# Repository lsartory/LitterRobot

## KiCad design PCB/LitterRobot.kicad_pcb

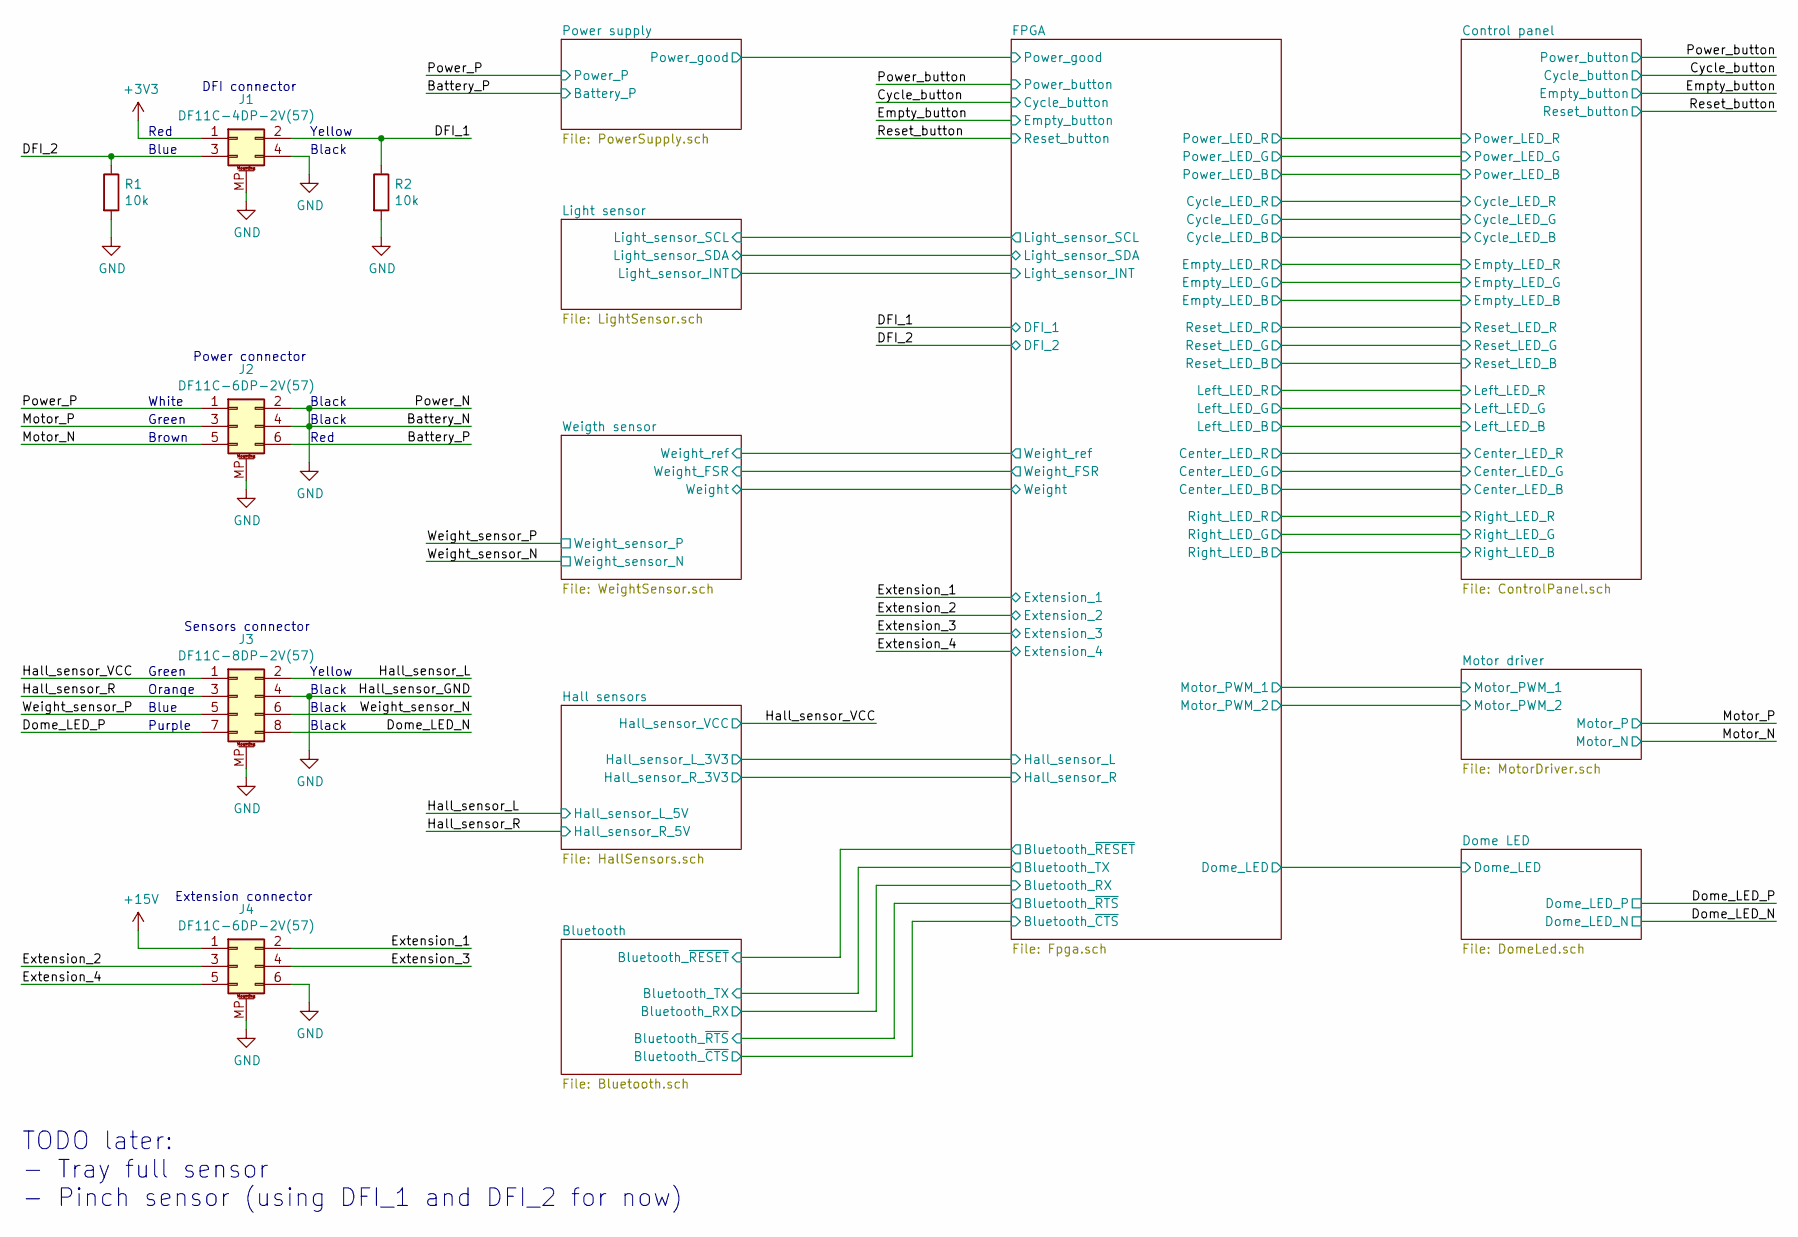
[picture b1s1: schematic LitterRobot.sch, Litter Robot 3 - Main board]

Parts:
J1: DF11C-4DP-2V(57); Hirose_DF11C-4DP-2V(57); Part_number DF11C-4DP-2V(57)
J2, J4: DF11C-6DP-2V(57); Hirose_DF11C-6DP-2V(57); Part_number DF11C-6DP-2V(57)
J3: DF11C-8DP-2V(57); Hirose_DF11C-8DP-2V(57); Part_number DF11C-8DP-2V(57)
R1, R2: 10k; R_0603_1608Metric; Part_number CR0603-FX-1002ELF

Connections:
+3V3: J1.1; also elsewhere on the board
+15V: J4.1; also elsewhere on the board
/Battery_P: J2.6; also elsewhere on the board
/DFI_1: J1.2, R2.1; also elsewhere on the board
/DFI_2: J1.3, R1.1; also elsewhere on the board
/Dome_LED_N: J3.8; also elsewhere on the board
/Dome_LED_P: J3.7; also elsewhere on the board
/Extension_1: J4.2; also elsewhere on the board
/Extension_2: J4.3; also elsewhere on the board
/Extension_3: J4.4; also elsewhere on the board
/Extension_4: J4.5; also elsewhere on the board
/Hall_sensor_L: J3.2; also elsewhere on the board
/Hall_sensor_R: J3.3; also elsewhere on the board
/Hall_sensor_VCC: J3.1; also elsewhere on the board
/Motor_N: J2.5; also elsewhere on the board
/Motor_P: J2.3; also elsewhere on the board
/Power_P: J2.1; also elsewhere on the board
/Weight_sensor_N: J3.6; also elsewhere on the board
/Weight_sensor_P: J3.5; also elsewhere on the board
GND: J1.4, J1.MP (MountPin), J2.2, J2.4, J2.MP (MountPin), J3.4, J3.MP (MountPin), J4.6, J4.MP (MountPin), R1.2, R2.2; also elsewhere on the board

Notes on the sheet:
Red
Blue
Yellow
Black
DFI connector
Power connector
White
Green
Brown
Sensors connector
Orange
Purple
Extension connector
TODO later: - Tray full sensor - Pinch sensor (using DFI_1 and DFI_2 for now)

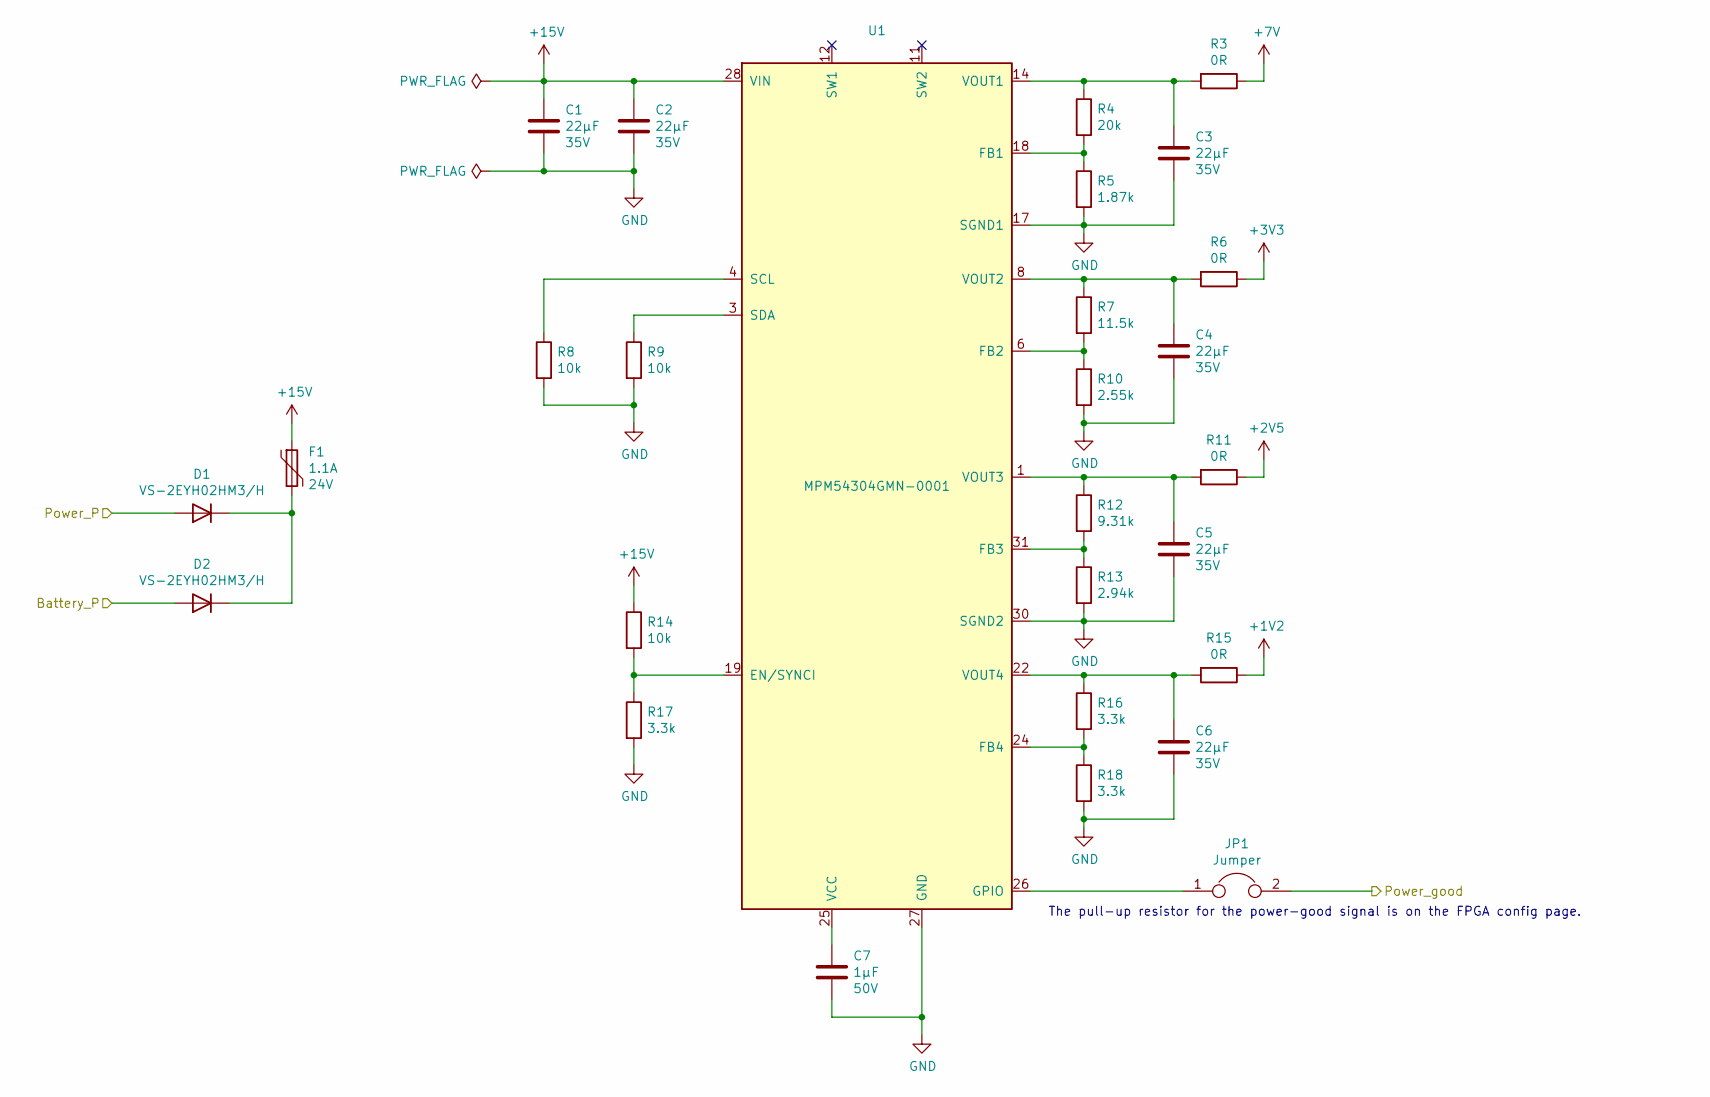
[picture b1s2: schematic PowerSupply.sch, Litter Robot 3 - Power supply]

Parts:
C1, C2, C3, C4, C5, C6: 22µF; C_1206_3216Metric; Voltage 35V; Part_number C3216X5R1V226M160AC
C7: 1µF; C_0603_1608Metric; Voltage 50V; Part_number C1608X5R1H105K080AB
D1, D2: VS-2EYH02HM3/H; Vishay_SlimSMAW; Part_number VS-2EYH02HM3/H
F1: 1.1A; Bel_Fuse_0ZCG; Voltage 24V; Part_number 0ZCG0110BF2B
JP1: Jumper; SolderJumper-2_P1.3mm_Bridged_RoundedPad1.0x1.5mm
R3, R6, R11, R15: 0R; R_0603_1608Metric; Part_number CR0603-J/-000ELF
R4: 20k; R_0603_1608Metric; Part_number CR0603-FX-2002ELF
R5: 1.87k; R_0603_1608Metric; Part_number CR0603-FX-1871ELF
R7: 11.5k; R_0603_1608Metric; Part_number CR0603-FX-1152ELF
R8, R9, R14: 10k; R_0603_1608Metric; Part_number CR0603-FX-1002ELF
R10: 2.55k; R_0603_1608Metric; Part_number CR0603-FX-2551ELF
R12: 9.31k; R_0603_1608Metric; Part_number CR0603-FX-9311ELF
R13: 2.94k; R_0603_1608Metric; Part_number CR0603-FX-2941ELF
R16, R17, R18: 3.3k; R_0603_1608Metric; Part_number CR0603-FX-3301ELF
U1: MPM54304GMN-0001; MPS_MPM54304_LGA33_7x7mm; Part_number MPM54304GMN-0001

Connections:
+1V2: R15.1; also elsewhere on the board
+2V5: R11.1; also elsewhere on the board
+3V3: R6.1; also elsewhere on the board
+7V: R3.1; also elsewhere on the board
+15V: C1.1, C2.1, F1.1, R14.1, U1.28 (VIN), U1.29 (VIN); also elsewhere on the board
/Battery_P: D2.2 (A); also elsewhere on the board
/FPGA/Power_good: JP1.2; also elsewhere on the board
/Power_P: D1.2 (A); also elsewhere on the board
GND: C1.2, C2.2, C3.2, C4.2, C5.2, C6.2, C7.2, R5.2, R8.2, R9.2, R10.2, R13.2, R17.2, R18.2, U1.2 (GND), U1.5 (GND), U1.7 (GND), U1.10 (GND), U1.13 (GND), U1.16 (GND), U1.17 (SGND1), U1.20 (GND), U1.21 (GND), U1.27 (GND), U1.30 (SGND2), U1.33 (GND); also elsewhere on the board
unnamed: C3.1, R3.2, R4.1, U1.14 (VOUT1), U1.15 (VOUT1)
unnamed: C4.1, R6.2, R7.1, U1.8 (VOUT2), U1.9 (VOUT2)
unnamed: C5.1, R11.2, R12.1, U1.1 (VOUT3), U1.32 (VOUT3)
unnamed: C6.1, R15.2, R16.1, U1.22 (VOUT4), U1.23 (VOUT4)
unnamed: C7.1, U1.25 (VCC)
unnamed: D1.1 (K), D2.1 (K), F1.2
unnamed: JP1.1, U1.26 (GPIO)
unnamed: R4.2, R5.1, U1.18 (FB1)
unnamed: R8.1, U1.4 (SCL)
unnamed: R9.1, U1.3 (SDA)
unnamed: R7.2, R10.1, U1.6 (FB2)
unnamed: R12.2, R13.1, U1.31 (FB3)
unnamed: R14.2, R17.1, U1.19 (EN/SYNCI)
unnamed: R16.2, R18.1, U1.24 (FB4)

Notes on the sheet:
The pull-up resistor for the power-good signal is on the FPGA config page.

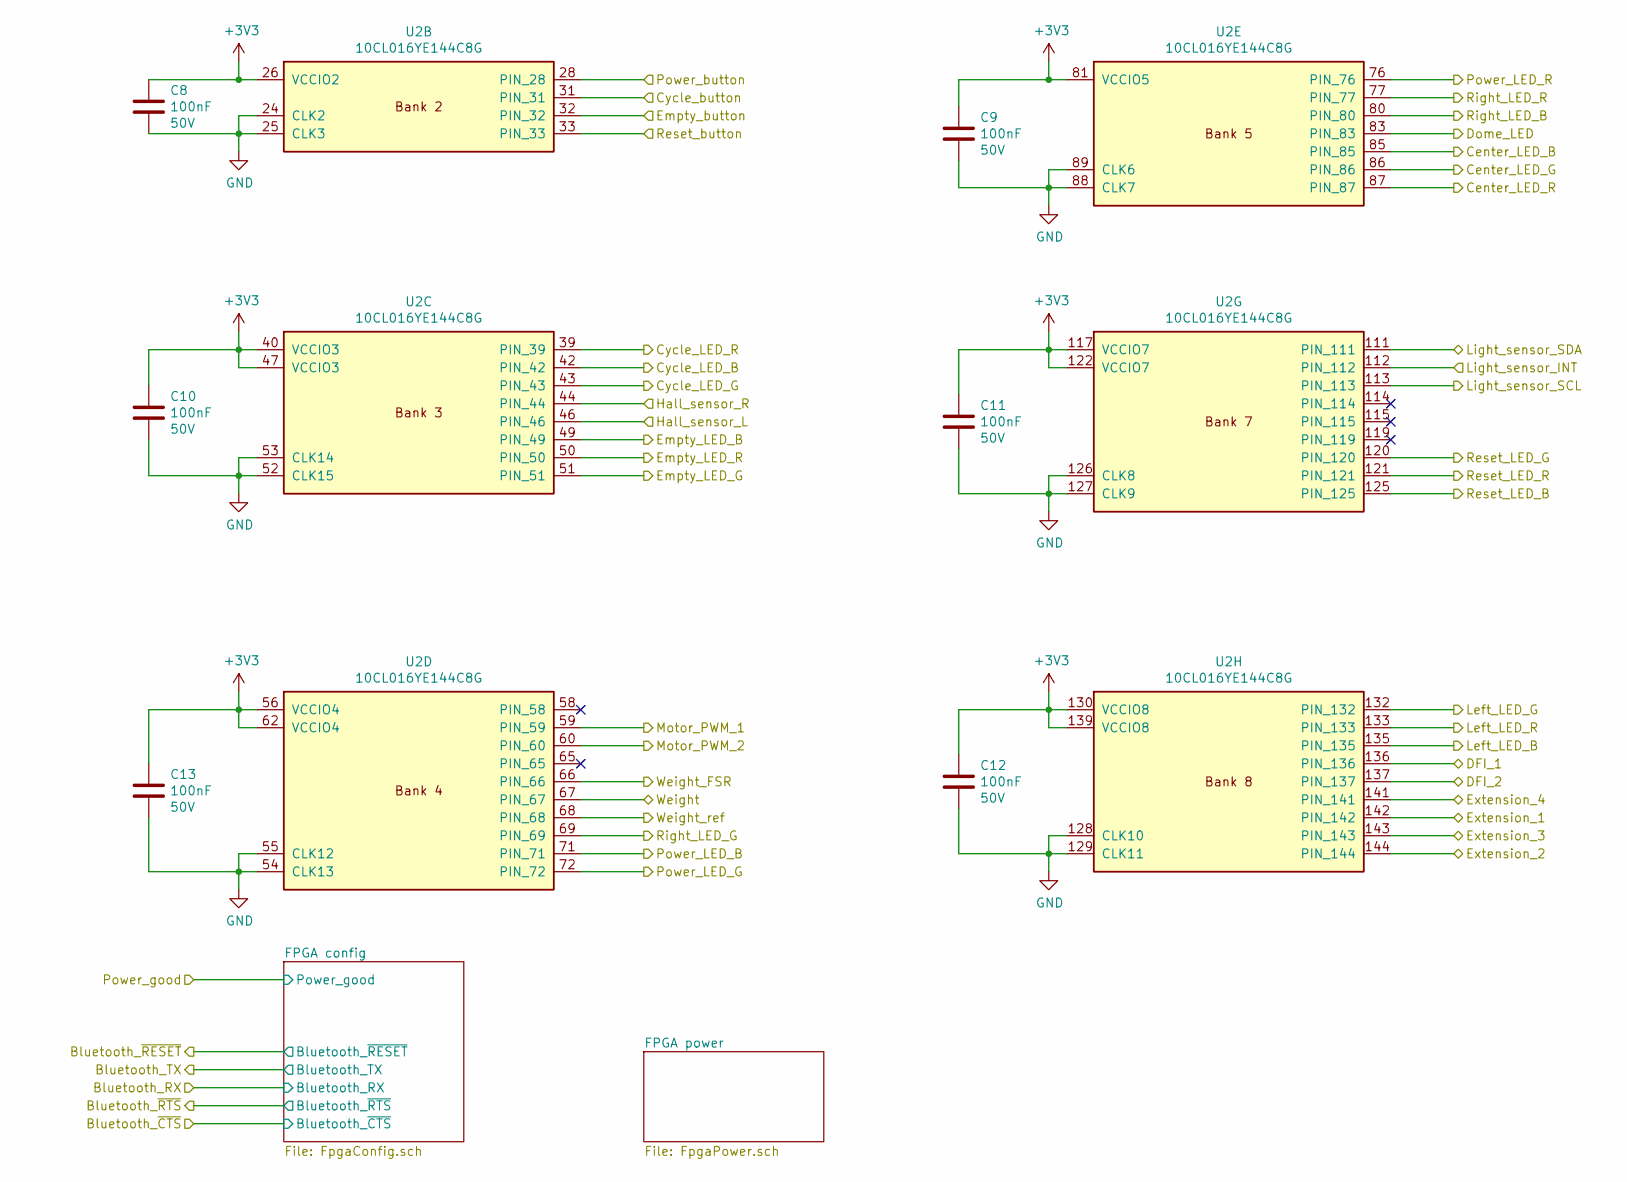
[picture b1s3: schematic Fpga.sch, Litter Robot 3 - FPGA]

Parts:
C8, C9, C10, C11, C12, C13: 100nF; C_0603_1608Metric; Voltage 50V; Part_number C1608X5R1H104K080AA
U2: 10CL016YE144C8G; Intel_EQFP-144-1EP_20x20mm_P0.5mm_EP6.7x6.7mm; Part_number 10CL016YE144C8G

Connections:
+3V3: C8.1, C9.1, C10.1, C11.1, C12.1, C13.1, U2.26 (VCCIO2), U2.40 (VCCIO3), U2.47 (VCCIO3), U2.56 (VCCIO4), U2.62 (VCCIO4), U2.81 (VCCIO5), U2.117 (VCCIO7), U2.122 (VCCIO7), U2.130 (VCCIO8), U2.139 (VCCIO8); also elsewhere on the board
/Control panel/Center_LED_B: U2.85 (PIN_85); also elsewhere on the board
/Control panel/Center_LED_G: U2.86 (PIN_86); also elsewhere on the board
/Control panel/Center_LED_R: U2.87 (PIN_87); also elsewhere on the board
/Control panel/Cycle_LED_B: U2.42 (PIN_42); also elsewhere on the board
/Control panel/Cycle_LED_G: U2.43 (PIN_43); also elsewhere on the board
/Control panel/Cycle_LED_R: U2.39 (PIN_39); also elsewhere on the board
/Control panel/Empty_LED_B: U2.49 (PIN_49); also elsewhere on the board
/Control panel/Empty_LED_G: U2.51 (PIN_51); also elsewhere on the board
/Control panel/Empty_LED_R: U2.50 (PIN_50); also elsewhere on the board
/Control panel/Left_LED_B: U2.135 (PIN_135); also elsewhere on the board
/Control panel/Left_LED_G: U2.132 (PIN_132); also elsewhere on the board
/Control panel/Left_LED_R: U2.133 (PIN_133); also elsewhere on the board
/Control panel/Power_LED_B: U2.71 (PIN_71); also elsewhere on the board
/Control panel/Power_LED_G: U2.72 (PIN_72); also elsewhere on the board
/Control panel/Power_LED_R: U2.76 (PIN_76); also elsewhere on the board
/Control panel/Reset_LED_B: U2.125 (PIN_125); also elsewhere on the board
/Control panel/Reset_LED_G: U2.120 (PIN_120); also elsewhere on the board
/Control panel/Reset_LED_R: U2.121 (PIN_121); also elsewhere on the board
/Control panel/Right_LED_B: U2.80 (PIN_80); also elsewhere on the board
/Control panel/Right_LED_G: U2.69 (PIN_69); also elsewhere on the board
/Control panel/Right_LED_R: U2.77 (PIN_77); also elsewhere on the board
/Cycle_button: U2.31 (PIN_31); also elsewhere on the board
/DFI_1: U2.136 (PIN_136); also elsewhere on the board
/DFI_2: U2.137 (PIN_137); also elsewhere on the board
/Dome LED/Dome_LED: U2.83 (PIN_83); also elsewhere on the board
/Extension_1: U2.142 (PIN_142); also elsewhere on the board
/Extension_2: U2.144 (PIN_144); also elsewhere on the board
/Extension_3: U2.143 (PIN_143); also elsewhere on the board
/Extension_4: U2.141 (PIN_141); also elsewhere on the board
/FPGA/Hall_sensor_L: U2.46 (PIN_46); also elsewhere on the board
/FPGA/Hall_sensor_R: U2.44 (PIN_44); also elsewhere on the board
/FPGA/Light_sensor_INT: U2.112 (PIN_112); also elsewhere on the board
/FPGA/Light_sensor_SCL: U2.113 (PIN_113); also elsewhere on the board
/FPGA/Light_sensor_SDA: U2.111 (PIN_111); also elsewhere on the board
/FPGA/Motor_PWM_1: U2.59 (PIN_59); also elsewhere on the board
/FPGA/Motor_PWM_2: U2.60 (PIN_60); also elsewhere on the board
/FPGA/Weight_ref: U2.68 (PIN_68); also elsewhere on the board
/Reset_button: U2.33 (PIN_33); also elsewhere on the board
/Weight_sensor_N: U2.67 (PIN_67); also elsewhere on the board
/Weight_sensor_P: U2.66 (PIN_66); also elsewhere on the board
GND: C8.2, C9.2, C10.2, C11.2, C12.2, C13.2, U2.24 (CLK2), U2.25 (CLK3), U2.52 (CLK15), U2.53 (CLK14), U2.54 (CLK13), U2.55 (CLK12), U2.88 (CLK7), U2.89 (CLK6), U2.126 (CLK8), U2.127 (CLK9), U2.128 (CLK10), U2.129 (CLK11); also elsewhere on the board

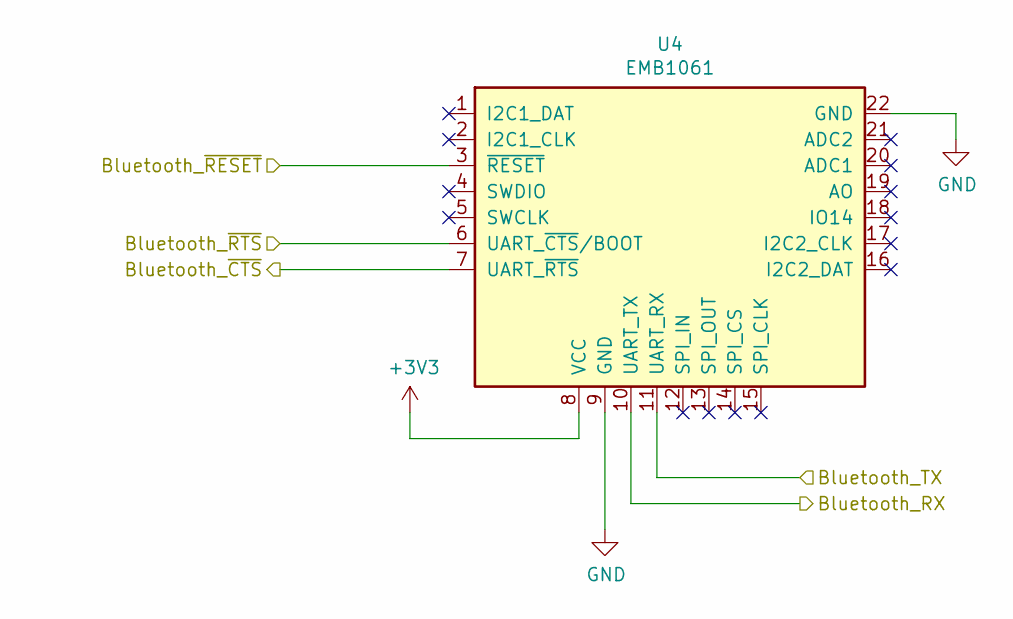
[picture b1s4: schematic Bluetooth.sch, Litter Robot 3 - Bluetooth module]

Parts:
U4: EMB1061; MXCHIP_EMB1061; Part_number 113990637

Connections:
+3V3: U4.8 (VCC); also elsewhere on the board
/Bluetooth/Bluetooth_RX: U4.10 (UART_TX); also elsewhere on the board
/Bluetooth/Bluetooth_TX: U4.11 (UART_RX); also elsewhere on the board
/Bluetooth/Bluetooth_~CTS: U4.7 (UART_~RTS); also elsewhere on the board
/Bluetooth/Bluetooth_~RESET: U4.3 (~RESET); also elsewhere on the board
/Bluetooth/Bluetooth_~RTS: U4.6 (UART_~CTS~/BOOT); also elsewhere on the board
GND: U4.9 (GND), U4.22 (GND); also elsewhere on the board

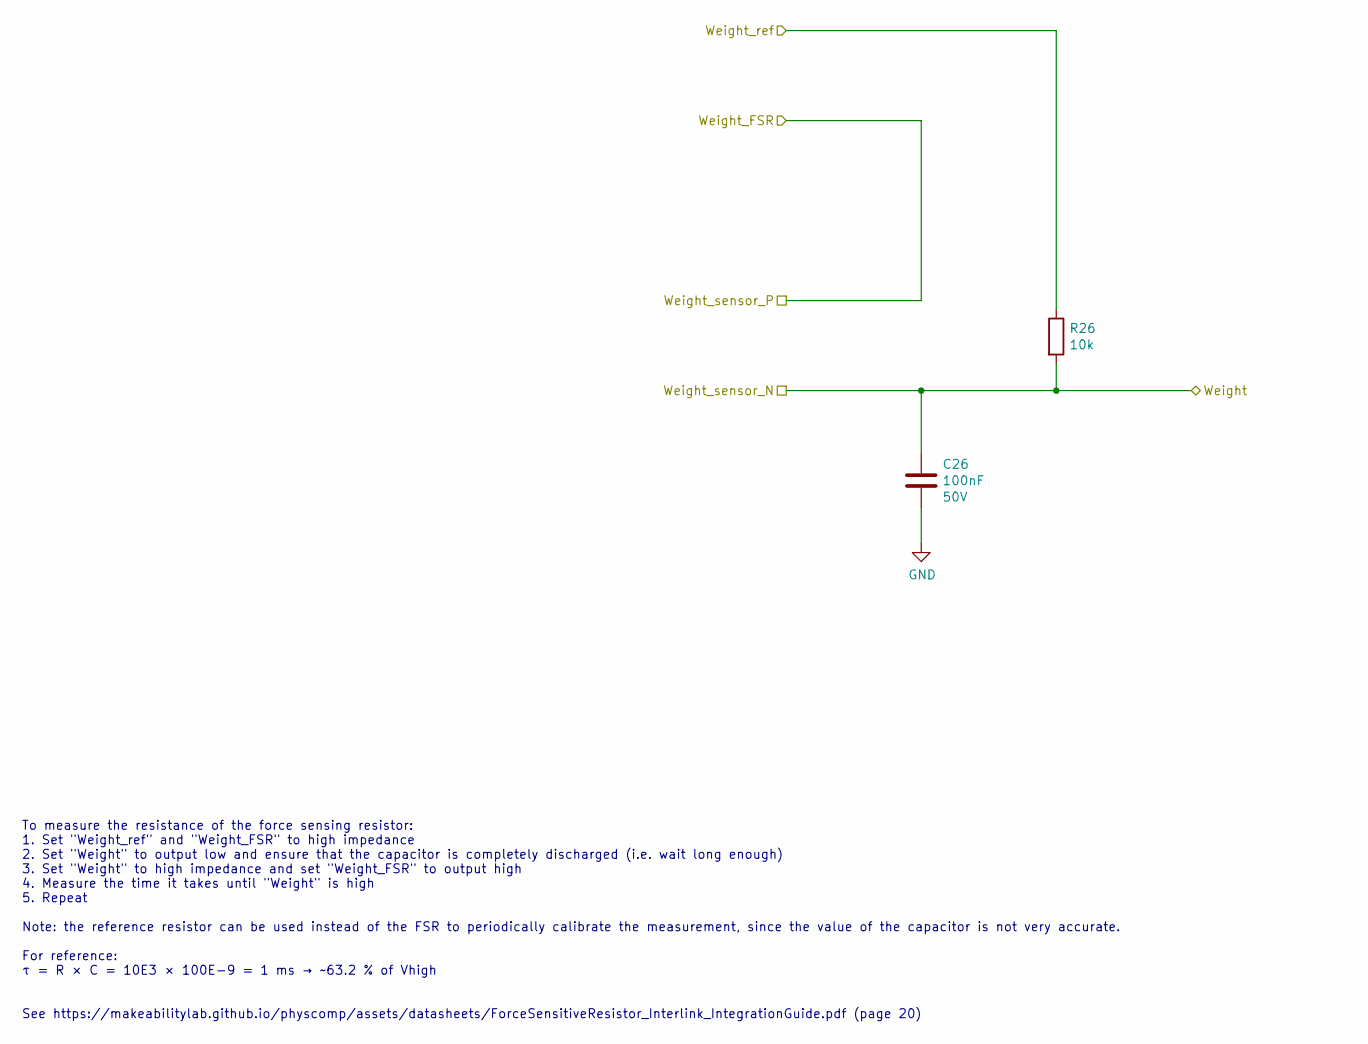
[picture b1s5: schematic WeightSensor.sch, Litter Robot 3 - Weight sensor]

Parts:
C26: 100nF; C_0603_1608Metric; Voltage 50V; Part_number C1608X5R1H104K080AA
R26: 10k; R_0603_1608Metric; Part_number CR0603-FX-1002ELF

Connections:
/FPGA/Weight_ref: R26.1; also elsewhere on the board
/Weight_sensor_N: C26.1, R26.2; also elsewhere on the board
GND: C26.2; also elsewhere on the board

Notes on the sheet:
To measure the resistance of the force sensing resistor: 1. Set "Weight_ref" and "Weight_FSR" to high impedance 2. Set "Weight" to output low and ensure that the capacitor is completely discharged (i.e. wait long enough) 3. Set "Weight" to high impedance and set "Weight_FSR" to output high 4. Measu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

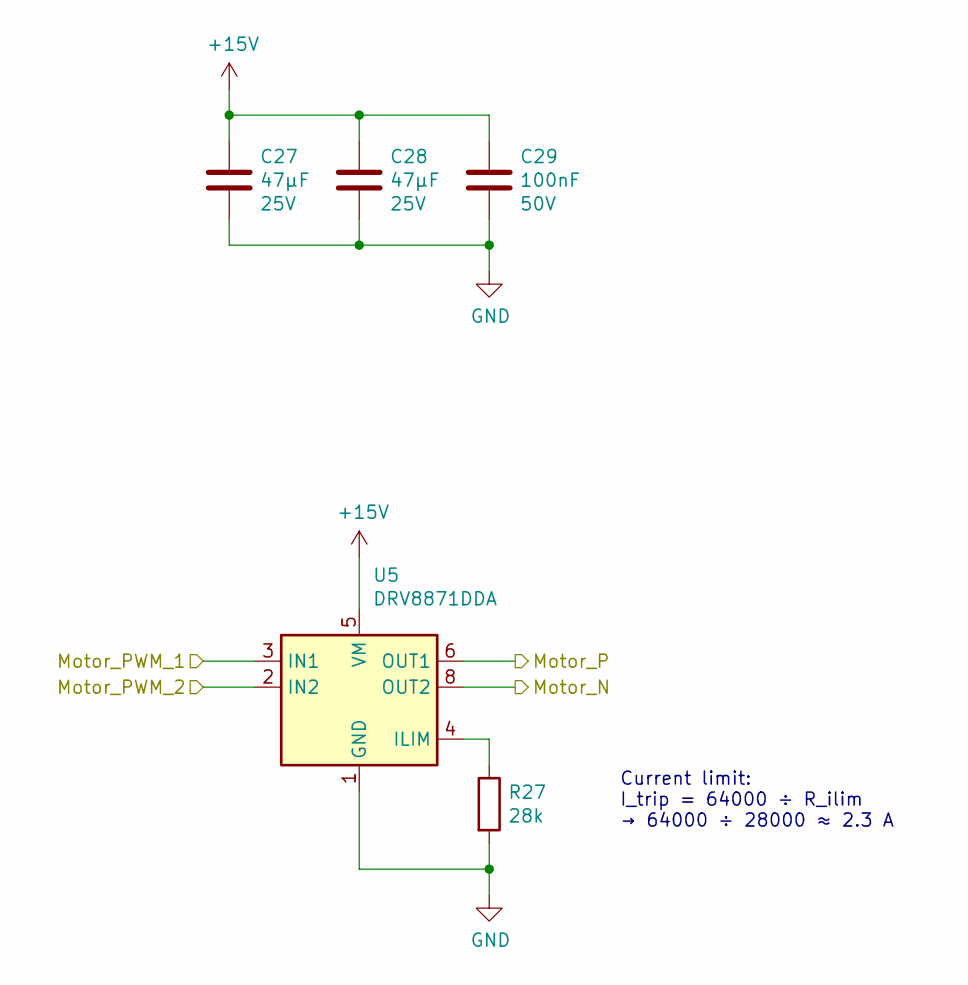
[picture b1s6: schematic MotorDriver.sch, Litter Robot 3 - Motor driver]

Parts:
C27, C28: 47µF; C_1206_3216Metric; Voltage 25V; Part_number C3216X5R1E476M160AC
C29: 100nF; C_0603_1608Metric; Voltage 50V; Part_number C1608X5R1H104K080AA
R27: 28k; R_0603_1608Metric; Part_number CR0603-FX-2802ELF
U5: DRV8871DDA; Texas_DRV8871; Part_number DRV8871DDARQ1

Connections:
+15V: C27.1, C28.1, C29.1, U5.5 (VM); also elsewhere on the board
/FPGA/Motor_PWM_1: U5.3 (IN1); also elsewhere on the board
/FPGA/Motor_PWM_2: U5.2 (IN2); also elsewhere on the board
/Motor_N: U5.8 (OUT2); also elsewhere on the board
/Motor_P: U5.6 (OUT1); also elsewhere on the board
GND: C27.2, C28.2, C29.2, R27.2, U5.1 (GND), U5.7 (GND), U5.9 (GND); also elsewhere on the board
unnamed: R27.1, U5.4 (ILIM)

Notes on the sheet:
Current limit: I_trip = 64000 ÷ R_ilim → 64000 ÷ 28000 ≈ 2.3 A

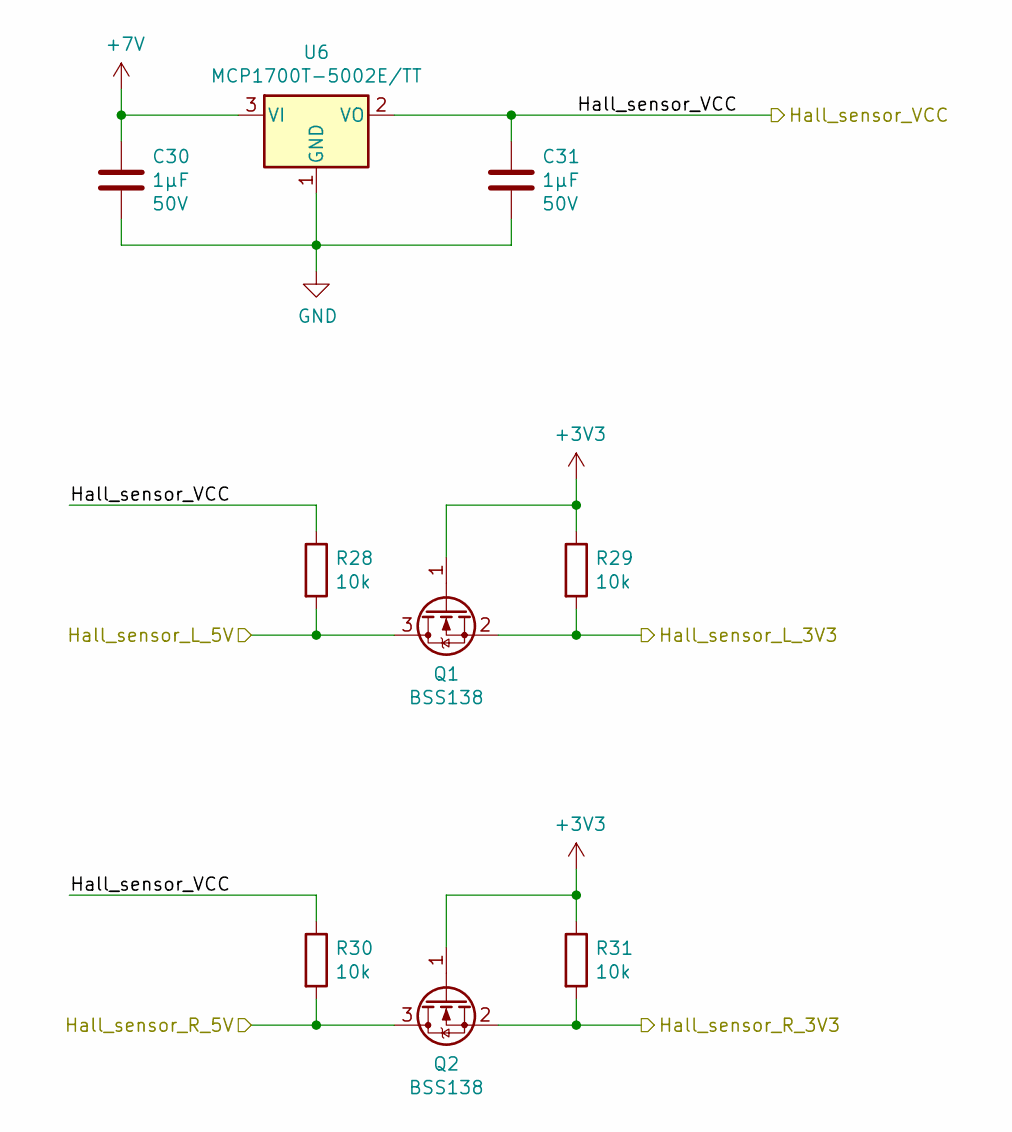
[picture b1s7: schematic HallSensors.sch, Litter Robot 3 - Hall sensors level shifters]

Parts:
C30, C31: 1µF; C_0603_1608Metric; Voltage 50V; Part_number C1608X5R1H105K080AB
Q1, Q2: BSS138; SOT-23; Part_number BSS138P,215
R28, R29, R30, R31: 10k; R_0603_1608Metric; Part_number CR0603-FX-1002ELF
U6: MCP1700T-5002E/TT; SOT-23; Part_number MCP1700T-5002E/TT

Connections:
+3V3: Q1.1 (G), Q2.1 (G), R29.1, R31.1; also elsewhere on the board
+7V: C30.1, U6.3 (VI); also elsewhere on the board
/FPGA/Hall_sensor_L: Q1.2 (S), R29.2; also elsewhere on the board
/FPGA/Hall_sensor_R: Q2.2 (S), R31.2; also elsewhere on the board
/Hall_sensor_L: Q1.3 (D), R28.2; also elsewhere on the board
/Hall_sensor_R: Q2.3 (D), R30.2; also elsewhere on the board
/Hall_sensor_VCC: C31.1, R28.1, R30.1, U6.2 (VO); also elsewhere on the board
GND: C30.2, C31.2, U6.1 (GND); also elsewhere on the board

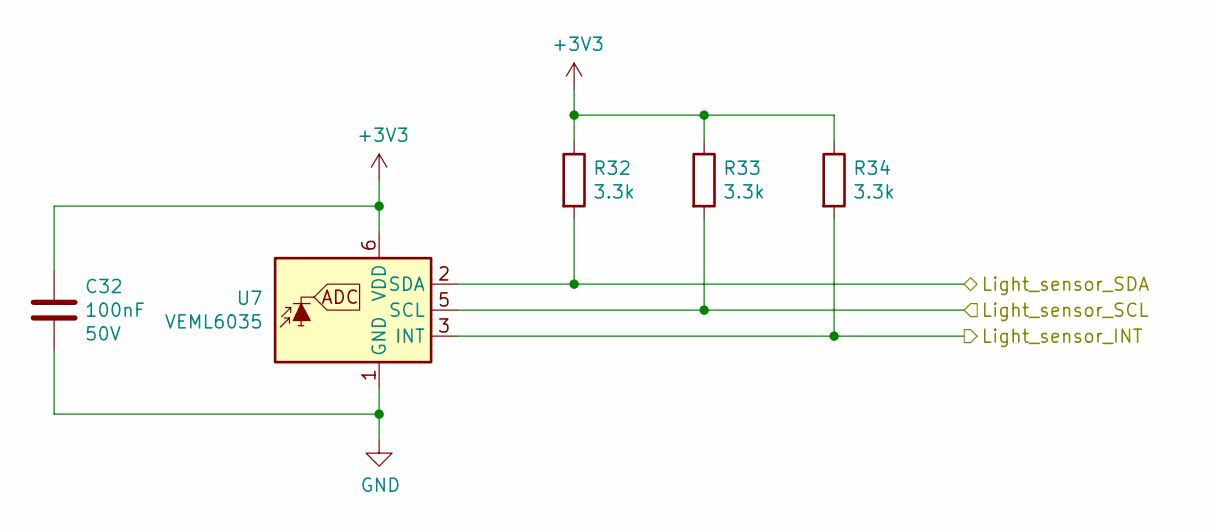
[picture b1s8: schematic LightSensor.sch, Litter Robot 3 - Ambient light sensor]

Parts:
C32: 100nF; C_0603_1608Metric; Voltage 50V; Part_number C1608X5R1H104K080AA
R32, R33, R34: 3.3k; R_0603_1608Metric; Part_number CR0603-FX-3301ELF
U7: VEML6035; Vishay_VEML6035; Part_number VEML6035

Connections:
+3V3: C32.1, R32.1, R33.1, R34.1, U7.6 (VDD); also elsewhere on the board
/FPGA/Light_sensor_INT: R34.2, U7.3 (INT); also elsewhere on the board
/FPGA/Light_sensor_SCL: R33.2, U7.5 (SCL); also elsewhere on the board
/FPGA/Light_sensor_SDA: R32.2, U7.2 (SDA); also elsewhere on the board
GND: C32.2, U7.1 (GND); also elsewhere on the board

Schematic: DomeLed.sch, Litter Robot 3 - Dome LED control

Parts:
D3: VS-2EYH02HM3/H; Vishay_SlimSMAW; Part_number VS-2EYH02HM3/H
Q3: BC817; SOT-23; Part_number BC817-25,215
R35: 178R; R_0603_1608Metric; Part_number CR0603-FX-1780ELF

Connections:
+7V: D3.2 (A); also elsewhere on the board
/Dome LED/Dome_LED: Q3.1 (B); also elsewhere on the board
/Dome_LED_N: Q3.3 (C); also elsewhere on the board
/Dome_LED_P: D3.1 (K); also elsewhere on the board
GND: R35.2; also elsewhere on the board
unnamed: Q3.2 (E), R35.1

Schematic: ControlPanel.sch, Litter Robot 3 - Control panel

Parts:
H1, H2, H3, H4, H5: MountingHole; MountingHole_4mm

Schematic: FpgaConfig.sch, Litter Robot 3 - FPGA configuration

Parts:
C14, C15: 100nF; C_0603_1608Metric; Voltage 50V; Part_number C1608X5R1H104K080AA
J5: TSM-105-01-S-DV; PinHeader_2x05_P2.54mm_Vertical_SMD; Part_number TSM-105-01-S-DV
R19, R20, R21, R22, R24: 10k; R_0603_1608Metric; Part_number CR0603-FX-1002ELF
R23: 1k; R_0603_1608Metric; Part_number CR0603-FX-1001ELF
R25: 24.9; R_0603_1608Metric; Part_number CR0603-FX-24R9ELF
TP1, TP2, TP3: TestPoint; TestPoint_Pad_D1.0mm
U2: 10CL016YE144C8G; Intel_EQFP-144-1EP_20x20mm_P0.5mm_EP6.7x6.7mm; Part_number 10CL016YE144C8G
U3: S25FL128SAGMFI000; SOIC-16W_7.5x10.3mm_P1.27mm; Part_number S25FL128SAGMFI000
X1: X1G0044510011; Seiko_SG5032CAN; Part_number X1G0044510011

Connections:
+2V5: R21.1, R22.1; also elsewhere on the board
+3V3: C14.1, C15.1, J5.4, R19.1, R20.1, R24.1, U2.17 (VCCIO1), U2.93 (VCCIO6), U2.96 (MSEL1), U3.2 (VCC), X1.4 (VCC); also elsewhere on the board
/Bluetooth/Bluetooth_RX: U2.103 (PIN_103); also elsewhere on the board
/Bluetooth/Bluetooth_TX: U2.99 (PIN_99); also elsewhere on the board
/Bluetooth/Bluetooth_~CTS: U2.101 (PIN_101); also elsewhere on the board
/Bluetooth/Bluetooth_~RESET: U2.98 (PIN_98); also elsewhere on the board
/Bluetooth/Bluetooth_~RTS: U2.100 (PIN_100); also elsewhere on the board
/FPGA/FPGA config/ASDO: U2.6 (ASDO), U3.15 (SI/IO0)
/FPGA/FPGA config/CLK_20MHz: U2.22 (CLK0), X1.3 (OUT)
/FPGA/FPGA config/DATA0: R25.1, U2.13 (DATA0)
/FPGA/FPGA config/DCLK: U2.12 (DCLK), U3.16 (SCK)
/FPGA/FPGA config/JTAG_TCK: J5.1, R23.1, U2.16 (TCK)
/FPGA/FPGA config/JTAG_TDI: J5.9, R22.2, U2.15 (TDI)
/FPGA/FPGA config/JTAG_TDO: J5.3, U2.20 (TDO)
/FPGA/FPGA config/JTAG_TMS: J5.5, R21.2, U2.18 (TMS)
/FPGA/FPGA config/~CS: U2.8 (~CSO), U3.7 (~CE)
/FPGA/Power_good: R19.2, U2.14 (~CONFIG); also elsewhere on the board
GND: C14.2, C15.2, J5.2, J5.10, R23.2, U2.21 (~CE), U2.23 (CLK1), U2.90 (CLK5), U2.91 (CLK4), U2.94 (MSEL0), U2.97 (MSEL2), U3.10 (GND), X1.2 (GND); also elsewhere on the board
unnamed: R20.2, U2.9 (~STATUS)
unnamed: R24.2, U2.92 (CONF_DONE)
unnamed: R25.2, U3.8 (SO/IO1)
unnamed: TP1.1, U2.7 (PIN_7)
unnamed: TP2.1, U2.10 (PIN_10)
unnamed: TP3.1, U2.11 (PIN_11)

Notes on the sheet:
JTAG debug port
MSEL[2..0] = "010" → Active serial, standard POR, 3.3 V
For other configuration device options: https://www.intel.com/content/www/us/en/programmable/support/support-resources/support-centers/configuration-support.html#intel-config-devices MT25QL128ABA8ESF-0SIT / MT25QL128ABA8ESF-0AAT MX25L12833FMI-10G S25FL128SAGMFI000
Intel® Cyclone® 10 LP Device Family Pin Connection Guidelines: https://www.intel.com/content/dam/www/programmable/us/en/pdfs/literature/dp/cyclone-10/pcg-01021.pdf

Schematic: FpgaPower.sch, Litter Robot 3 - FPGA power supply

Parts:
C16, C17, C18, C19, C20, C21, C22, C23, C24, C25: 100nF; C_0603_1608Metric; Voltage 50V; Part_number C1608X5R1H104K080AA
U2: 10CL016YE144C8G; Intel_EQFP-144-1EP_20x20mm_P0.5mm_EP6.7x6.7mm; Part_number 10CL016YE144C8G

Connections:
+1V2: C16.1, C17.1, C18.1, C19.1, C20.1, C21.1, C22.1, C23.1, U2.1 (VCCD_PLL3), U2.5 (VCCINT), U2.29 (VCCINT), U2.34 (VCCINT), U2.37 (VCCD_PLL1), U2.38 (VCCINT), U2.45 (VCCINT), U2.61 (VCCINT), U2.70 (VCCINT), U2.73 (VCCD_PLL4), U2.78 (VCCINT), U2.84 (VCCINT), U2.102 (VCCINT), U2.109 (VCCD_PLL2), U2.116 (VCCINT), U2.124 (VCCINT), U2.134 (VCCINT), U2.138 (VCCINT); also elsewhere on the board
+2V5: C24.1, C25.1, U2.3 (VCCA3), U2.35 (VCCA1), U2.75 (VCCA4), U2.107 (VCCA2); also elsewhere on the board
GND: C16.2, C17.2, C18.2, C19.2, C20.2, C21.2, C22.2, C23.2, C24.2, C25.2, U2.2 (GNDA3), U2.4 (GND), U2.19 (GND), U2.27 (GND), U2.30 (GND), U2.36 (GNDA1), U2.41 (GND), U2.48 (GND), U2.57 (GND), U2.63 (GND), U2.64 (GND), U2.74 (GNDA4), U2.79 (GND), U2.82 (GND), U2.95 (GND), U2.104 (GND), U2.108 (GNDA2), U2.110 (GND), U2.118 (GND), U2.123 (GND), U2.131 (GND), U2.140 (GND), U2.145 (EP); also elsewhere on the board

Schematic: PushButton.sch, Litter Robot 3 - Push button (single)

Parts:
R38: 10k; R_0603_1608Metric; Part_number CR0603-FX-1002ELF
SW1: PCB_Push_Button; PCB_Push_Button_5mm_0.4mm

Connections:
+3V3: R38.1; also elsewhere on the board
GND: SW1.2; also elsewhere on the board

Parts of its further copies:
R36: 10k; R_0603_1608Metric; Part_number CR0603-FX-1002ELF
SW4: PCB_Push_Button; PCB_Push_Button_5mm_0.4mm

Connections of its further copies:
+3V3: R36.1; also elsewhere on the board
GND: SW4.2; also elsewhere on the board

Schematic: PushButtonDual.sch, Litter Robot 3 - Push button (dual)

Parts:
R37: 10k; R_0603_1608Metric; Part_number CR0603-FX-1002ELF
SW2, SW3: PCB_Push_Button; PCB_Push_Button_5mm_0.4mm

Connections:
+3V3: R37.1; also elsewhere on the board
/Cycle_button: R37.2, SW2.1, SW3.1; also elsewhere on the board
GND: SW2.2, SW3.2; also elsewhere on the board

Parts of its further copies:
R39: 10k; R_0603_1608Metric; Part_number CR0603-FX-1002ELF
SW5, SW6: PCB_Push_Button; PCB_Push_Button_5mm_0.4mm

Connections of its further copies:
+3V3: R39.1; also elsewhere on the board
/Reset_button: R39.2, SW5.1, SW6.1; also elsewhere on the board
GND: SW5.2, SW6.2; also elsewhere on the board
